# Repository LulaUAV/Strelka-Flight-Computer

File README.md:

# Strelka-Flight-Computer
Strelka exists in the family of rocket dog flight computers. This flight computer is fully capable of deploying recovery events.

Strelka (Стрелка, "little arrow") was a dog that spent a day in space aboard Korabl-Sputnik 2 (Sputnik 5) on 19 August 1960 before safely returning to Earth.

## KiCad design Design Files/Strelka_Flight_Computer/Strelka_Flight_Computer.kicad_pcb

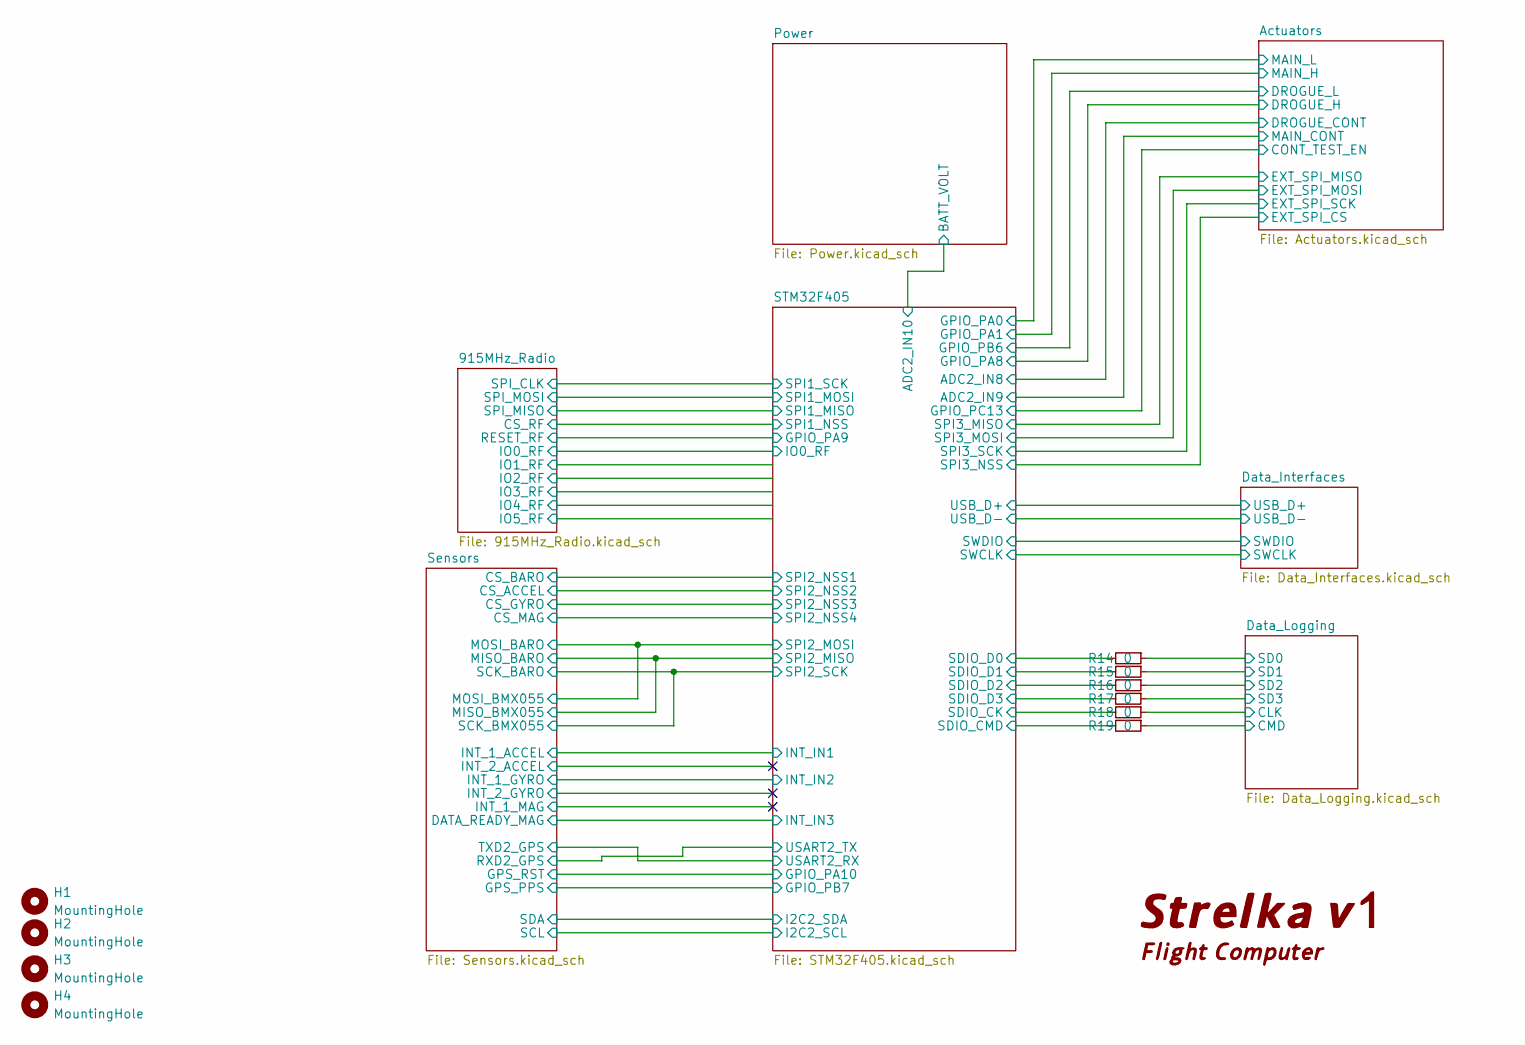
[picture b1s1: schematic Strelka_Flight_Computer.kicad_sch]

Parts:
H1, H2, H3, H4: MountingHole; MountingHole_2.5mm_Pad
R14, R15, R16, R17, R18, R19: 0; R_0603_1608Metric_Pad0.98x0.95mm_HandSolder

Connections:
/Data_Logging/CLK: R18.1; also elsewhere on the board
/Data_Logging/CMD: R19.1; also elsewhere on the board
/Data_Logging/SD0: R14.1; also elsewhere on the board
/Data_Logging/SD1: R15.1; also elsewhere on the board
/Data_Logging/SD2: R16.1; also elsewhere on the board
/Data_Logging/SD3: R17.1; also elsewhere on the board
/STM32F405/SDIO_CK: R18.2; also elsewhere on the board
/STM32F405/SDIO_CMD: R19.2; also elsewhere on the board
/STM32F405/SDIO_D0: R14.2; also elsewhere on the board
/STM32F405/SDIO_D1: R15.2; also elsewhere on the board
/STM32F405/SDIO_D2: R16.2; also elsewhere on the board
/STM32F405/SDIO_D3: R17.2; also elsewhere on the board

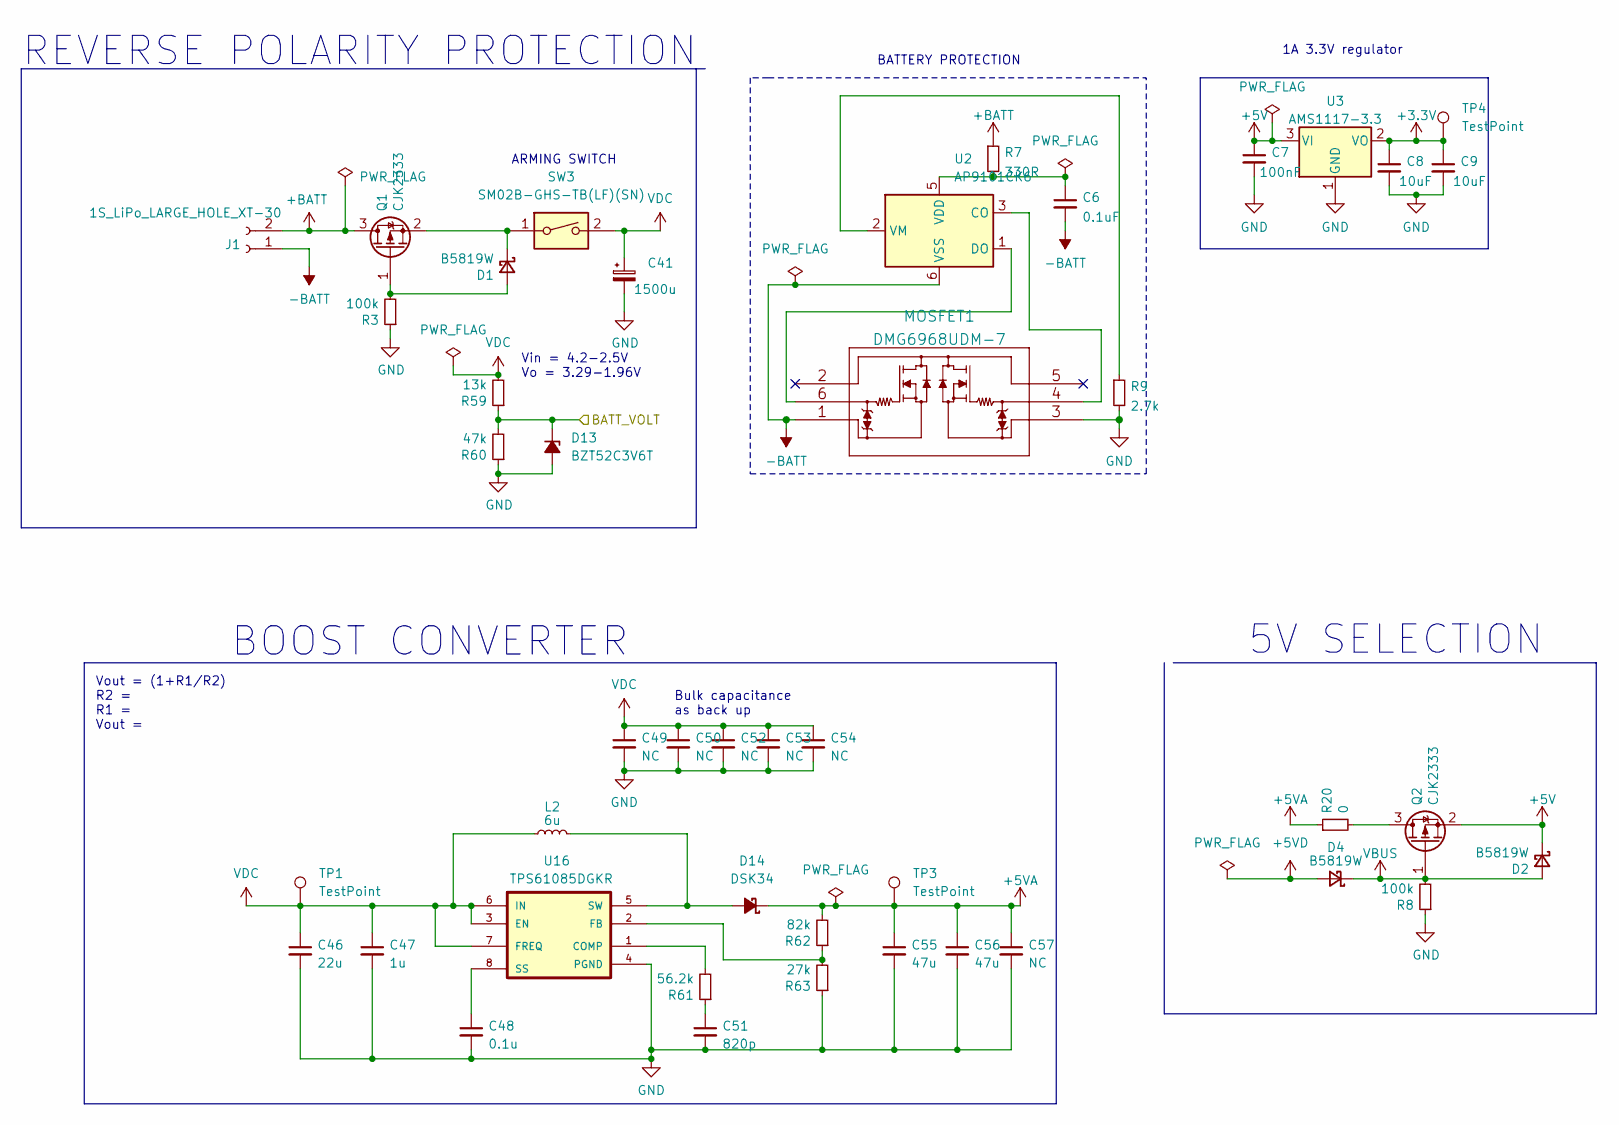
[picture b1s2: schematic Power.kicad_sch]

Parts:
C6: 0.1uF; C_0603_1608Metric
C7: 100nF; C_0603_1608Metric_Pad1.08x0.95mm_HandSolder
C8, C9: 10uF; C_0603_1608Metric_Pad1.08x0.95mm_HandSolder
C41: 1500u; ULR158M0JF1ARR; LCSC# C248440
C46: 22u; C_0603_1608Metric
C47: 1u; C_0603_1608Metric
C48: 0.1u; C_0603_1608Metric
C49, C50, C52, C53, C54: NC; C_0603_1608Metric
C51: 820p; C_0603_1608Metric
C55, C56: 47u; C_0805_2012Metric
C57: NC; C_0805_2012Metric
D1, D2, D4: B5819W; D_SOD-123; LCSC# C8598
D13: BZT52C3V6T; D_SOD-523; LCSC# C2858499
D14: DSK34; D_SOD-123; LCSC# C908230
J1: 1S_LiPo_LARGE_HOLE_XT-30; AMASS_XT30PW-M_1x02_P2.50mm_Horizontal
L2: 6u; L_Bourns_SRP5030T; LCSC# C1329837
MOSFET1: DMG6968UDM-7; LCSC# C151635
Q1, Q2: CJK2333; SOT-23; LCSC# C504109
R3, R8: 100k; R_0603_1608Metric
R7: 330R; R_0603_1608Metric
R9: 2.7k; R_0603_1608Metric
R20: 0; R_0603_1608Metric
R59: 13k; R_0603_1608Metric; LCSC# C137796
R60: 47k; R_0603_1608Metric; LCSC# C105579
R61: 56.2k; R_0603_1608Metric; LCSC# C105579
R62: 82k; R_0603_1608Metric; LCSC# C105579
R63: 27k; R_0603_1608Metric; LCSC# C105579
SW3: SM02B-GHS-TB(LF)(SN); SM02BGHSTBLFSN; LCSC# C189893
TP1, TP3, TP4: TestPoint; TestPoint_Pad_1.0x1.0mm
U2: AP9101CK6; SOT-23-6; LCSC# C151339
U3: AMS1117-3.3; SOT-223-3_TabPin2; LCSC# C173386
U16: TPS61085DGKR; SOP65P490X110-8N; LCSC# C113659

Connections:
+3V3: C8.1, C9.1, TP4.1, U3.2 (VO); also elsewhere on the board
+5V: C7.1, D2.1 (K), Q2.2 (S), U3.3 (VI)
+5VA: C55.1, C56.1, C57.1, D14.1 (K), R20.1, R62.2, TP3.1
+5VD: D4.2 (A); also elsewhere on the board
+BATT: J1.2, Q1.3 (D), R7.1
-BATT: C6.2, J1.1, MOSFET1.1 (S1), U2.6 (VSS)
/Power/BATT_VOLT: D13.1 (K), R59.1, R60.2; also elsewhere on the board
GND: C7.2, C8.2, C9.2, C41.2, C46.2, C47.2, C48.2, C49.2, C50.2, C51.2, C52.2, C53.2, C54.2, C55.2, C56.2, C57.2, D13.2 (A), MOSFET1.3 (S2), R3.1, R8.1, R9.2, R60.1, R63.1, U3.1 (GND), U16.4 (PGND); also elsewhere on the board
unnamed: C6.1, R7.2, U2.5 (VDD)
unnamed: C48.1, U16.8 (SS)
unnamed: C51.1, R61.1
unnamed: D1.1 (K), Q1.2 (S), SW3.1
unnamed: D1.2 (A), Q1.1 (G), R3.2
unnamed: D14.2 (A), L2.2, U16.5 (SW)
unnamed: MOSFET1.4 (G2), U2.3 (CO)
unnamed: MOSFET1.6 (G1), U2.1 (DO)
unnamed: Q2.3 (D), R20.2
unnamed: R9.1, U2.2 (VM)
unnamed: R61.2, U16.1 (COMP)
unnamed: R62.1, R63.2, U16.2 (FB)
VBUS: D2.2 (A), D4.1 (K), Q2.1 (G), R8.2; also elsewhere on the board
VDC: C41.1, C46.1, C47.1, C49.1, C50.1, C52.1, C53.1, C54.1, L2.1, R59.2, SW3.2, TP1.1, U16.3 (EN), U16.6 (IN), U16.7 (FREQ); also elsewhere on the board

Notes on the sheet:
5V SELECTION
BOOST CONVERTER
1A 3.3V regulator
REVERSE POLARITY PROTECTION
Vout = (1+R1/R2) R2 = R1 = Vout =
BATTERY PROTECTION
Bulk capacitance as back up
ARMING SWITCH
Vin = 4.2-2.5V Vo = 3.29-1.96V

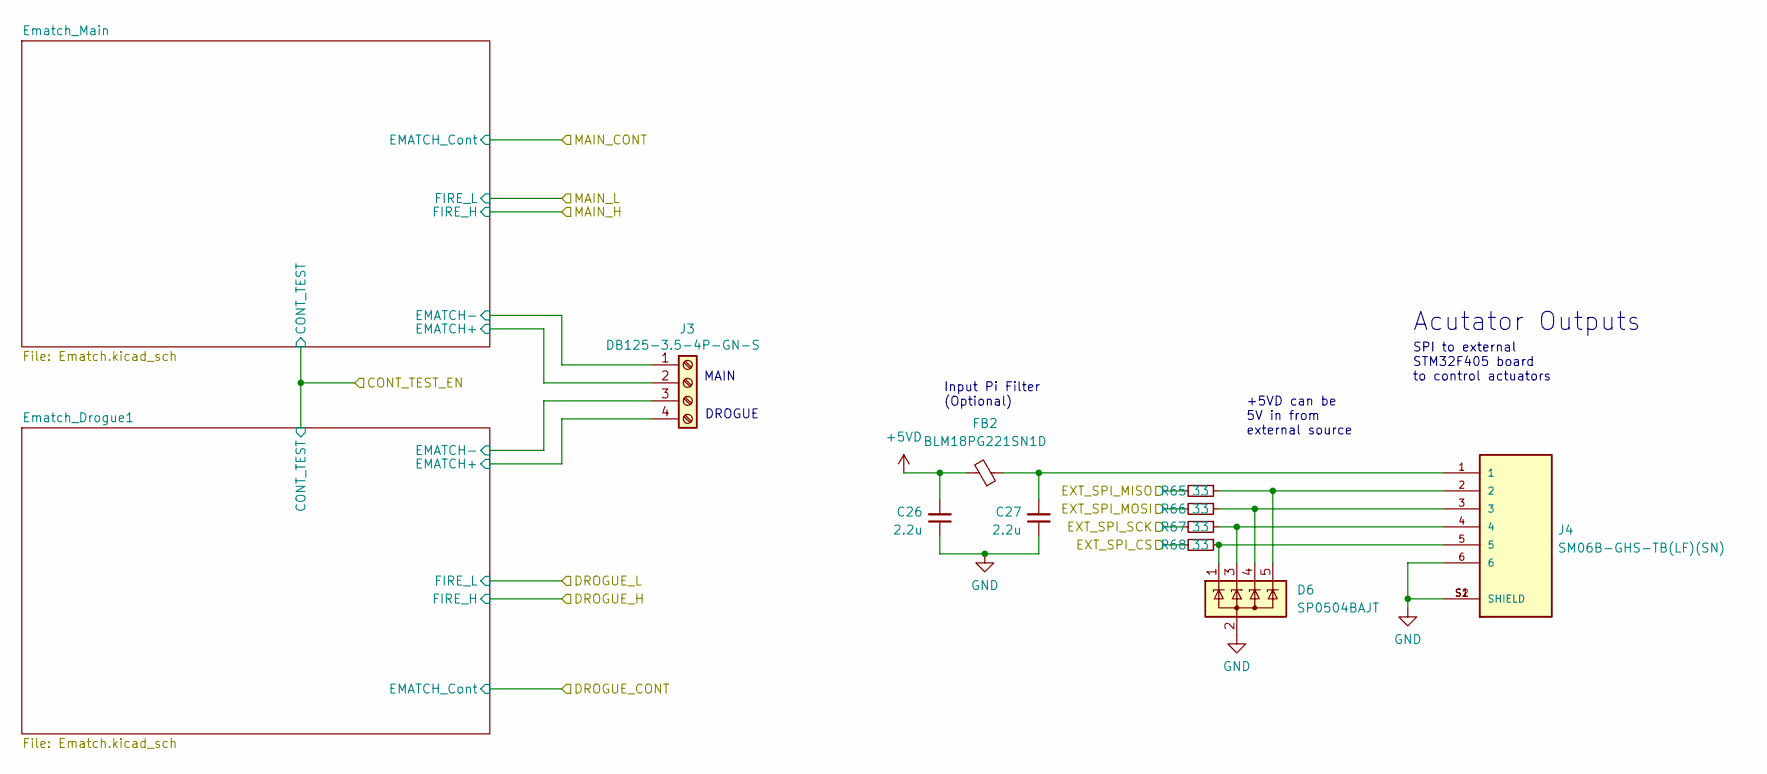
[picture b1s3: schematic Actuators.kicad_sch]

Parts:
C26, C27: 2.2u; C_0603_1608Metric
D6: SP0504BAJT; SOT-353_SC-70-5; LCSC# C5116451
FB2: BLM18PG221SN1D; L_0603_1608Metric; LCSC# C80165
J3: DB125-3.5-4P-GN-S; TerminalBlock_4Ucon_1x04_P3.50mm_Horizontal; LCSC# C2757925
J4: SM06B-GHS-TB(LF)(SN); JST_SM06B-GHS-TB(LF)(SN); LCSC# C133065
R65, R66, R67, R68: 33; R_0603_1608Metric_Pad0.98x0.95mm_HandSolder

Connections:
+5VD: C26.2, FB2.2; also elsewhere on the board
/Actuators/EXT_SPI_CS: R68.2; also elsewhere on the board
/Actuators/EXT_SPI_MISO: R65.2; also elsewhere on the board
/Actuators/EXT_SPI_MOSI: R66.2; also elsewhere on the board
/Actuators/EXT_SPI_SCK: R67.2; also elsewhere on the board
/Actuators/Ematch_Drogue1/EMATCH+: J3.4; also elsewhere on the board
/Actuators/Ematch_Drogue1/EMATCH-: J3.3; also elsewhere on the board
/Actuators/Ematch_Main/EMATCH+: J3.2; also elsewhere on the board
/Actuators/Ematch_Main/EMATCH-: J3.1; also elsewhere on the board
GND: C26.1, C27.1, D6.2 (A), J4.6, J4.S1 (SHIELD), J4.S2 (SHIELD); also elsewhere on the board
unnamed: C27.2, FB2.1, J4.1
unnamed: D6.1 (K), J4.5, R68.1
unnamed: D6.3 (K), J4.4, R67.1
unnamed: D6.4 (K), J4.3, R66.1
unnamed: D6.5 (K), J4.2, R65.1

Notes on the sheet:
DROGUE
+5VD can be 5V in from external source
Acutator Outputs
SPI to external STM32F405 board to control actuators
Input Pi Filter (Optional)
MAIN

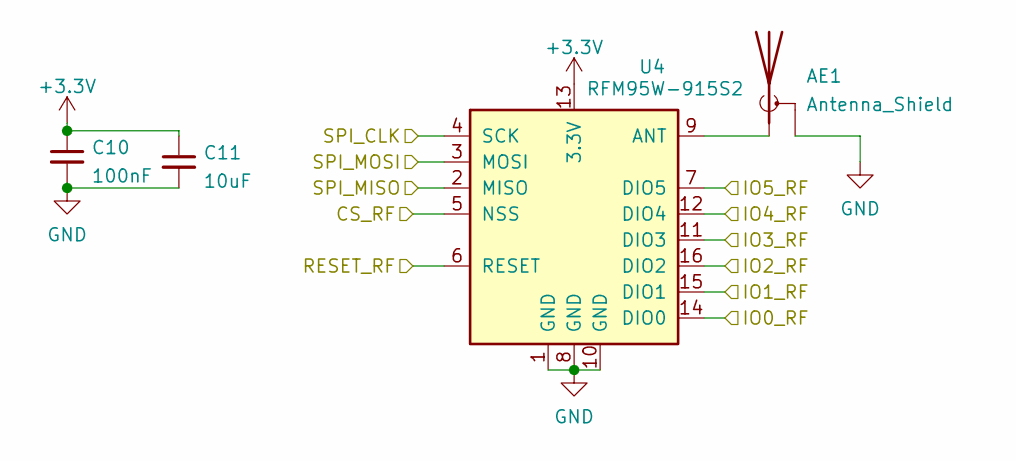
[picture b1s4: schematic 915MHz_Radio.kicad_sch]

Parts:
AE1: Antenna_Shield; SMA_Amphenol_132134_Vertical; LCSC# C496550
C10: 100nF; C_0603_1608Metric_Pad1.08x0.95mm_HandSolder
C11: 10uF; C_0603_1608Metric_Pad1.08x0.95mm_HandSolder
U4: RFM95W-915S2; HOPERF_RFM9XW_SMD; LCSC# C2844473

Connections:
+3V3: C10.1, C11.1, U4.13 (3.3V); also elsewhere on the board
/915MHz_Radio/CS_RF: U4.5 (NSS); also elsewhere on the board
/915MHz_Radio/IO0_RF: U4.14 (DIO0); also elsewhere on the board
/915MHz_Radio/IO1_RF: U4.15 (DIO1)
/915MHz_Radio/IO2_RF: U4.16 (DIO2)
/915MHz_Radio/IO3_RF: U4.11 (DIO3)
/915MHz_Radio/IO4_RF: U4.12 (DIO4)
/915MHz_Radio/IO5_RF: U4.7 (DIO5)
/915MHz_Radio/RESET_RF: U4.6 (RESET); also elsewhere on the board
/915MHz_Radio/SPI_CLK: U4.4 (SCK); also elsewhere on the board
/915MHz_Radio/SPI_MISO: U4.2 (MISO); also elsewhere on the board
/915MHz_Radio/SPI_MOSI: U4.3 (MOSI); also elsewhere on the board
GND: AE1.2 (Shield), C10.2, C11.2, U4.1 (GND), U4.8 (GND), U4.10 (GND); also elsewhere on the board
unnamed: AE1.1 (A), U4.9 (ANT)

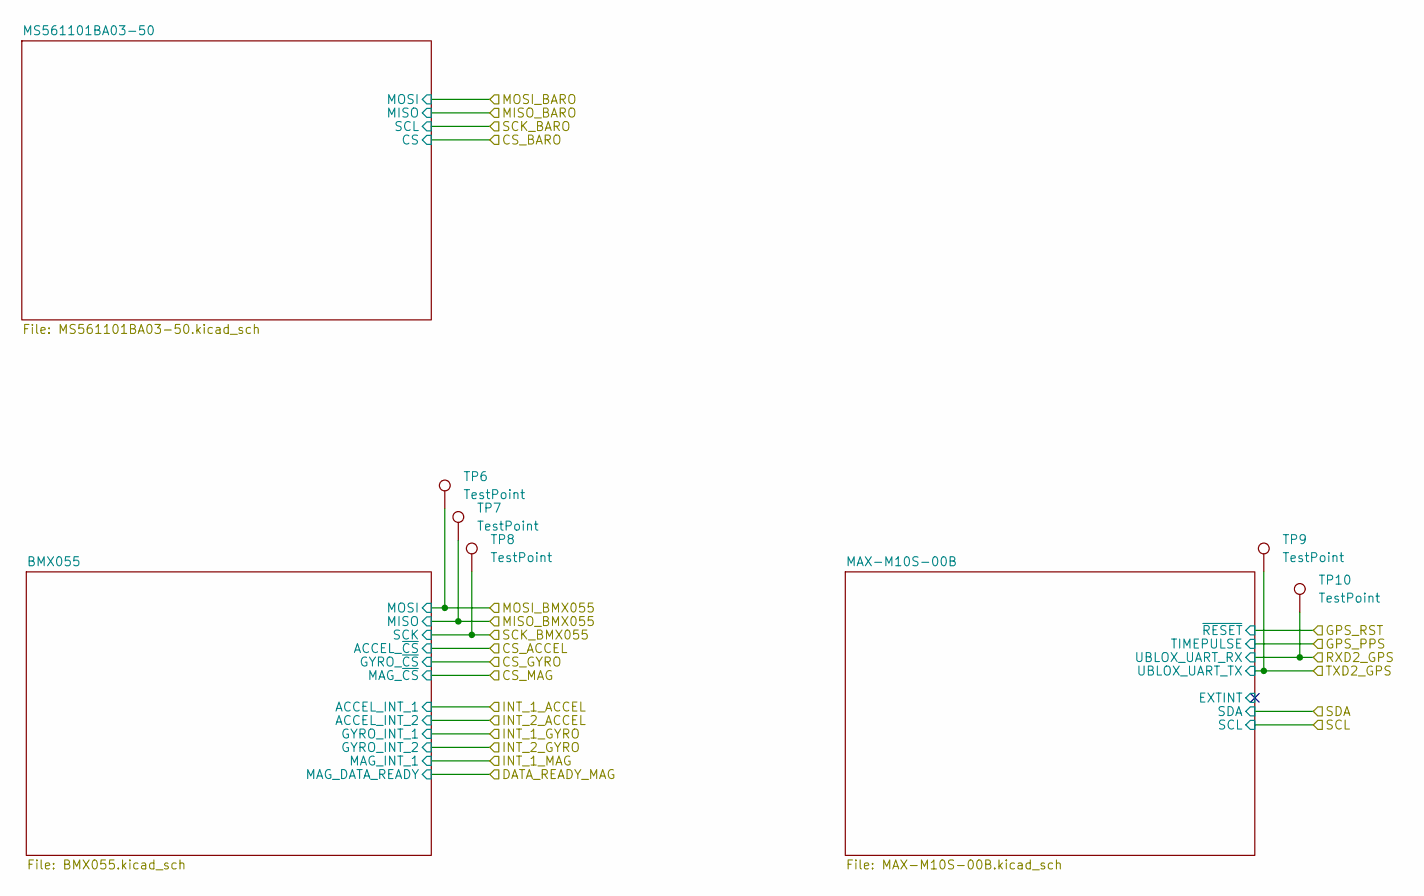
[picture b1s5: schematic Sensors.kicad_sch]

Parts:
TP6, TP7, TP8, TP9, TP10: TestPoint; TestPoint_Pad_1.0x1.0mm

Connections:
/STM32F405/SPI2_MISO: TP7.1; also elsewhere on the board
/STM32F405/SPI2_MOSI: TP6.1; also elsewhere on the board
/STM32F405/SPI2_SCK: TP8.1; also elsewhere on the board
/STM32F405/USART2_RX: TP9.1; also elsewhere on the board
/STM32F405/USART2_TX: TP10.1; also elsewhere on the board

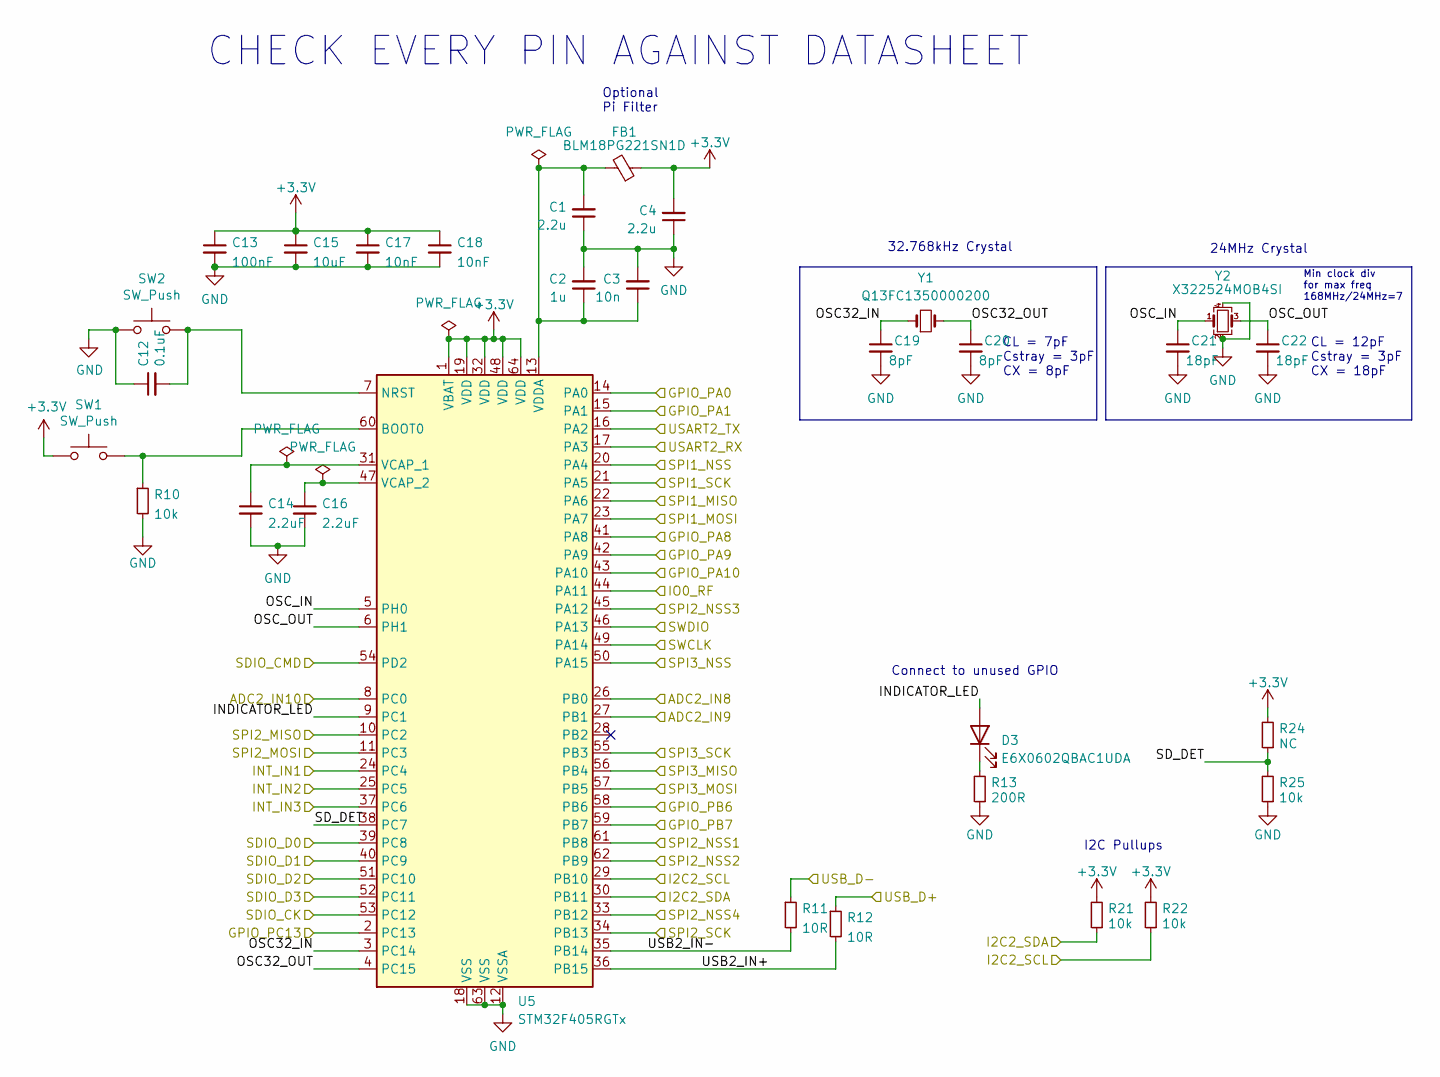
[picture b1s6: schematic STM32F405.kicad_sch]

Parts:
C1, C4: 2.2u; C_0603_1608Metric
C2: 1u; C_0603_1608Metric
C3: 10n; C_0603_1608Metric
C12: 0.1uF; C_0603_1608Metric_Pad1.08x0.95mm_HandSolder
C13: 100nF; C_0603_1608Metric_Pad1.08x0.95mm_HandSolder
C14, C16: 2.2uF; C_0603_1608Metric_Pad1.08x0.95mm_HandSolder
C15: 10uF; C_0603_1608Metric_Pad1.08x0.95mm_HandSolder
C17, C18: 10nF; C_0603_1608Metric_Pad1.08x0.95mm_HandSolder
C19, C20: 8pF; C_0603_1608Metric_Pad1.08x0.95mm_HandSolder
C21, C22: 18pF; C_0603_1608Metric_Pad1.08x0.95mm_HandSolder
D3: E6X0602QBAC1UDA; LED_0603_1608Metric_Pad1.05x0.95mm_HandSolder; LCSC# C375467
FB1: BLM18PG221SN1D; L_0603_1608Metric; LCSC# C80165
R10: 10k; R_0603_1608Metric
R11, R12: 10R; R_0603_1608Metric
R13: 200R; R_0603_1608Metric_Pad0.98x0.95mm_HandSolder
R21, R22, R25: 10k; R_0603_1608Metric_Pad0.98x0.95mm_HandSolder
R24: NC; R_0603_1608Metric_Pad0.98x0.95mm_HandSolder
SW1, SW2: SW_Push; SW_Push_SPST_NO_Alps_SKRK
U5: STM32F405RGTx; LQFP-64_10x10mm_P0.5mm; LCSC# C15742
Y1: Q13FC1350000200; Crystal_SMD_3215-2Pin_3.2x1.5mm; LCSC# C48615
Y2: X322524MOB4SI; Crystal_SMD_3225-4Pin_3.2x2.5mm; LCSC# C70590

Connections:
+3V3: C4.2, C13.1, C15.1, C17.1, C18.1, FB1.1, R21.2, R22.2, R24.2, SW1.1, U5.1 (VBAT), U5.19 (VDD), U5.32 (VDD), U5.48 (VDD), U5.64 (VDD); also elsewhere on the board
/915MHz_Radio/CS_RF: U5.20 (PA4); also elsewhere on the board
/915MHz_Radio/IO0_RF: U5.44 (PA11); also elsewhere on the board
/915MHz_Radio/RESET_RF: U5.42 (PA9); also elsewhere on the board
/915MHz_Radio/SPI_CLK: U5.21 (PA5); also elsewhere on the board
/915MHz_Radio/SPI_MISO: U5.22 (PA6); also elsewhere on the board
/915MHz_Radio/SPI_MOSI: U5.23 (PA7); also elsewhere on the board
/Actuators/CONT_TEST_EN: U5.2 (PC13); also elsewhere on the board
/Actuators/DROGUE_CONT: U5.26 (PB0); also elsewhere on the board
/Actuators/DROGUE_H: U5.41 (PA8); also elsewhere on the board
/Actuators/DROGUE_L: U5.58 (PB6); also elsewhere on the board
/Actuators/EXT_SPI_CS: U5.50 (PA15); also elsewhere on the board
/Actuators/EXT_SPI_MISO: U5.56 (PB4); also elsewhere on the board
/Actuators/EXT_SPI_MOSI: U5.57 (PB5); also elsewhere on the board
/Actuators/EXT_SPI_SCK: U5.55 (PB3); also elsewhere on the board
/Actuators/MAIN_CONT: U5.27 (PB1); also elsewhere on the board
/Actuators/MAIN_H: U5.15 (PA1); also elsewhere on the board
/Actuators/MAIN_L: U5.14 (PA0); also elsewhere on the board
/Data_Interfaces/SWCLK: U5.49 (PA14); also elsewhere on the board
/Data_Interfaces/SWDIO: U5.46 (PA13); also elsewhere on the board
/Data_Interfaces/USB_D+: R12.1; also elsewhere on the board
/Data_Interfaces/USB_D-: R11.1; also elsewhere on the board
/Power/BATT_VOLT: U5.8 (PC0); also elsewhere on the board
/STM32F405/GPIO_PA10: U5.43 (PA10); also elsewhere on the board
/STM32F405/GPIO_PB7: U5.59 (PB7); also elsewhere on the board
/STM32F405/I2C2_SCL: R22.1, U5.29 (PB10); also elsewhere on the board
/STM32F405/I2C2_SDA: R21.1, U5.30 (PB11); also elsewhere on the board
/STM32F405/INDICATOR_LED: D3.2 (A), U5.9 (PC1)
/STM32F405/INT_IN1: U5.24 (PC4); also elsewhere on the board
/STM32F405/INT_IN2: U5.25 (PC5); also elsewhere on the board
/STM32F405/INT_IN3: U5.37 (PC6); also elsewhere on the board
/STM32F405/OSC32_IN: C19.1, U5.3 (PC14), Y1.1
/STM32F405/OSC32_OUT: C20.1, U5.4 (PC15), Y1.2
/STM32F405/OSC_IN: C21.1, U5.5 (PH0), Y2.1
/STM32F405/OSC_OUT: C22.1, U5.6 (PH1), Y2.3
/STM32F405/SDIO_CK: U5.53 (PC12); also elsewhere on the board
/STM32F405/SDIO_CMD: U5.54 (PD2); also elsewhere on the board
/STM32F405/SDIO_D0: U5.39 (PC8); also elsewhere on the board
/STM32F405/SDIO_D1: U5.40 (PC9); also elsewhere on the board
/STM32F405/SDIO_D2: U5.51 (PC10); also elsewhere on the board
/STM32F405/SDIO_D3: U5.52 (PC11); also elsewhere on the board
/STM32F405/SD_DET: R24.1, R25.2, U5.38 (PC7)
/STM32F405/SPI2_MISO: U5.10 (PC2); also elsewhere on the board
/STM32F405/SPI2_MOSI: U5.11 (PC3); also elsewhere on the board
/STM32F405/SPI2_NSS1: U5.61 (PB8); also elsewhere on the board
/STM32F405/SPI2_NSS2: U5.62 (PB9); also elsewhere on the board
/STM32F405/SPI2_NSS3: U5.45 (PA12); also elsewhere on the board
/STM32F405/SPI2_NSS4: U5.33 (PB12); also elsewhere on the board
/STM32F405/SPI2_SCK: U5.34 (PB13); also elsewhere on the board
/STM32F405/USART2_RX: U5.17 (PA3); also elsewhere on the board
/STM32F405/USART2_TX: U5.16 (PA2); also elsewhere on the board
/STM32F405/USB2_IN+: R12.2, U5.36 (PB15)
/STM32F405/USB2_IN-: R11.2, U5.35 (PB14)
GND: C1.1, C2.2, C3.2, C4.1, C12.1, C13.2, C14.2, C15.2, C16.2, C17.2, C18.2, C19.2, C20.2, C21.2, C22.2, R10.2, R13.1, R25.1, SW2.1, U5.12 (VSSA), U5.18 (VSS), U5.63 (VSS), Y2.2, Y2.4; also elsewhere on the board
unnamed: C1.2, C2.1, C3.1, FB1.2, U5.13 (VDDA)
unnamed: C12.2, SW2.2, U5.7 (NRST)
unnamed: C14.1, U5.31 (VCAP_1)
unnamed: C16.1, U5.47 (VCAP_2)
unnamed: D3.1 (K), R13.2
unnamed: R10.1, SW1.2, U5.60 (BOOT0)

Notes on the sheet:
Connect to unused GPIO
24MHz Crystal
CL = 7pF Cstray = 3pF CX = 8pF
32.768kHz Crystal
I2C Pullups
CHECK EVERY PIN AGAINST DATASHEET
CL = 12pF Cstray = 3pF CX = 18pF
Optional Pi Filter
Min clock div for max freq 168MHz/24MHz=7

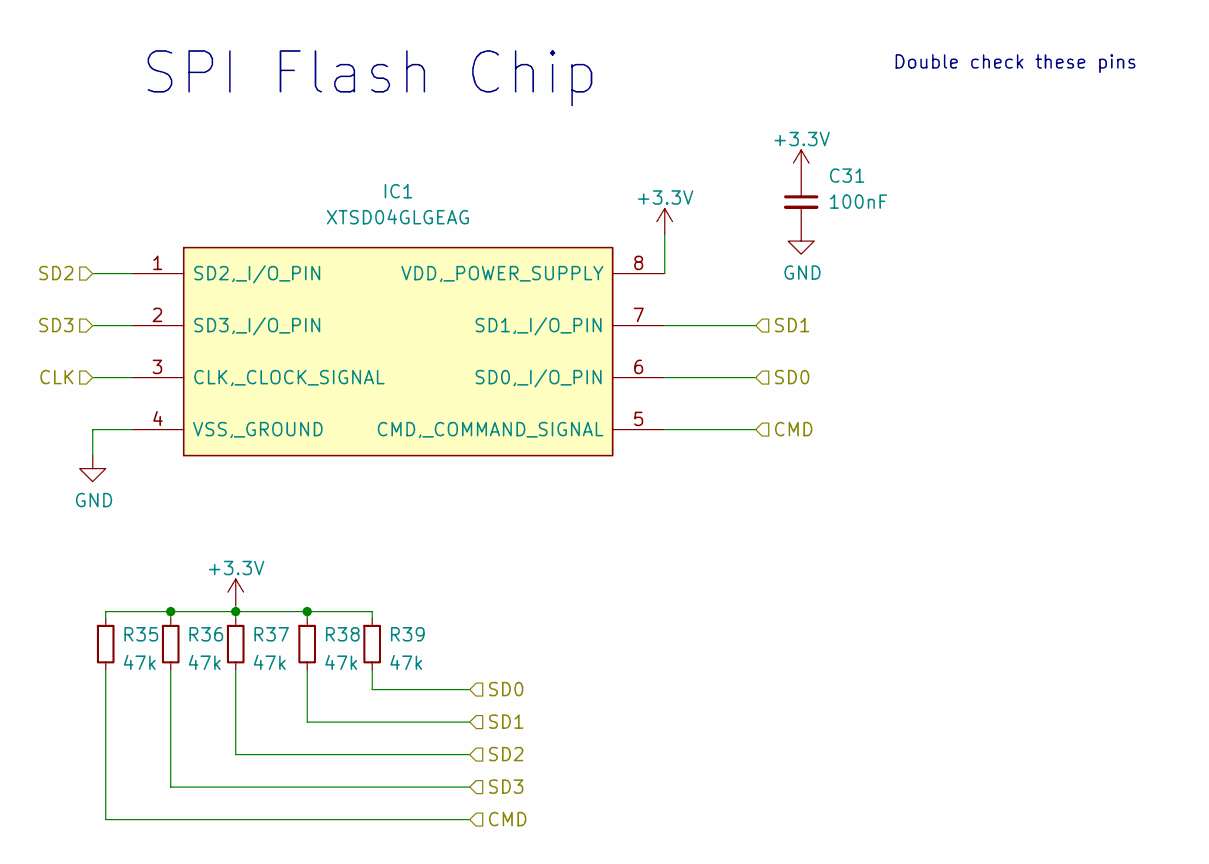
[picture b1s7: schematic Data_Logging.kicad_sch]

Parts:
C31: 100nF; C_0603_1608Metric
IC1: XTSD04GLGEAG; SON127P800X600X95-8N; LCSC# C558839
R35, R36, R37, R38, R39: 47k; R_0603_1608Metric

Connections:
+3V3: C31.1, IC1.8 (VDD,_POWER_SUPPLY), R35.1, R36.1, R37.1, R38.1, R39.1; also elsewhere on the board
/Data_Logging/CLK: IC1.3 (CLK,_CLOCK_SIGNAL); also elsewhere on the board
/Data_Logging/CMD: IC1.5 (CMD,_COMMAND_SIGNAL), R35.2; also elsewhere on the board
/Data_Logging/SD0: IC1.6 (SD0,_I/O_PIN), R39.2; also elsewhere on the board
/Data_Logging/SD1: IC1.7 (SD1,_I/O_PIN), R38.2; also elsewhere on the board
/Data_Logging/SD2: IC1.1 (SD2,_I/O_PIN), R37.2; also elsewhere on the board
/Data_Logging/SD3: IC1.2 (SD3,_I/O_PIN), R36.2; also elsewhere on the board
GND: C31.2, IC1.4 (VSS,_GROUND); also elsewhere on the board

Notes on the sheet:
SPI Flash Chip
Double check these pins

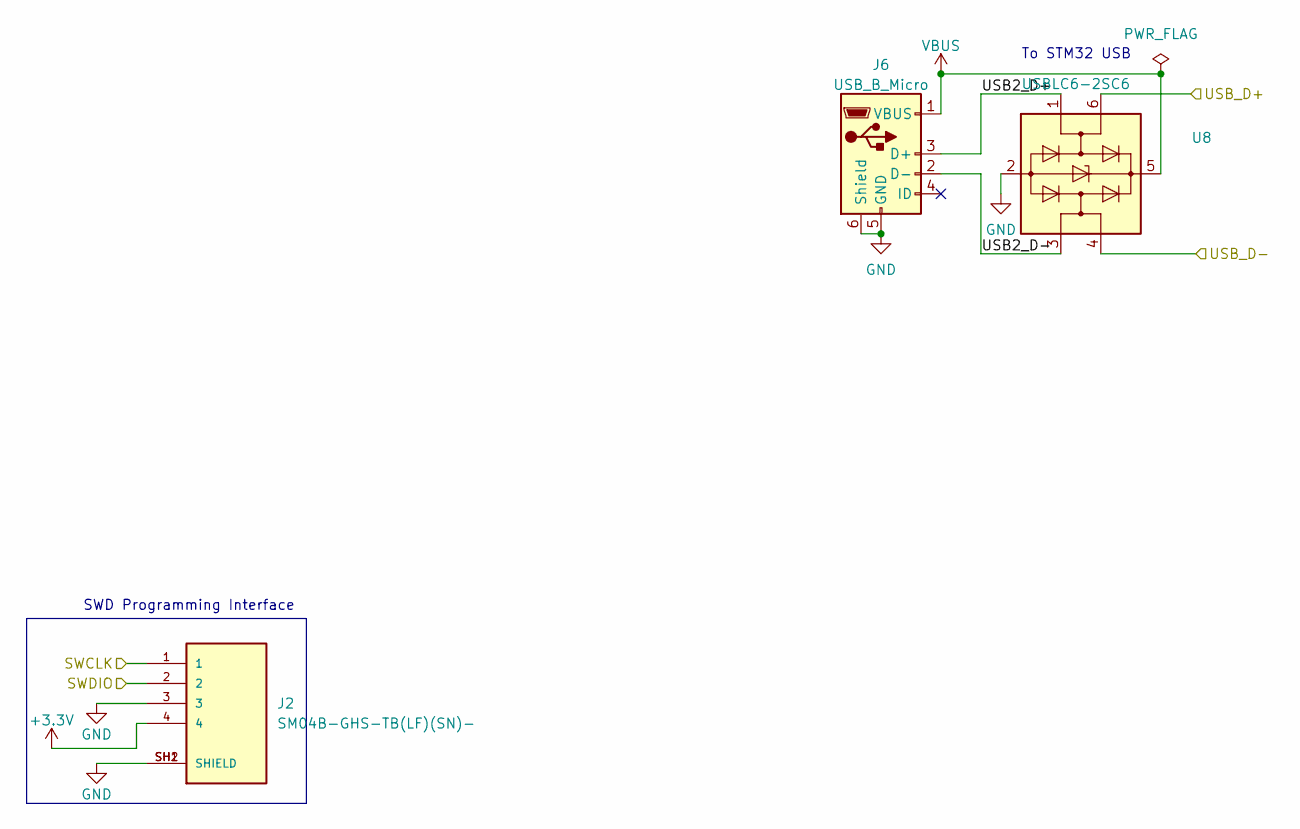
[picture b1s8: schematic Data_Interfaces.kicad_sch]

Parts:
J2: SM04B-GHS-TB(LF)(SN)-; JST_SM04B-GHS-TB(LF)(SN)-; LCSC# C189895
J6: USB_B_Micro; USB_Micro-B_Molex-105017-0001
U8: USBLC6-2SC6; SOT-23-6; LCSC# C2687116

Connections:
+3V3: J2.4; also elsewhere on the board
/Data_Interfaces/SWCLK: J2.1; also elsewhere on the board
/Data_Interfaces/SWDIO: J2.2; also elsewhere on the board
/Data_Interfaces/USB2_D+: J6.3 (D+), U8.1 (I/O1)
/Data_Interfaces/USB2_D-: J6.2 (D-), U8.3 (I/O2)
/Data_Interfaces/USB_D+: U8.6 (I/O1); also elsewhere on the board
/Data_Interfaces/USB_D-: U8.4 (I/O2); also elsewhere on the board
GND: J2.3, J2.SH1 (SHIELD), J2.SH2 (SHIELD), J6.5 (GND), J6.6 (Shield), U8.2 (GND); also elsewhere on the board
VBUS: J6.1 (VBUS), U8.5 (VBUS); also elsewhere on the board

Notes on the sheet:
To STM32 USB
SWD Programming Interface

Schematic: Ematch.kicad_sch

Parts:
D9: 1SS388; D_SOD-523; LCSC# C2987059
I2: AL5809-30S1-7; D_SOD-123; LCSC# C151325
Q8, Q9: AO3401A; SOT-23; LCSC# C347476
Q10: AP2300; SOT-23; LCSC# C360338
Q11: MMBT2222; SOT-23; LCSC# C8512
R47: 2R; R_2512_6332Metric; LCSC# C91926
R48, R51, R53, R54: 1k; R_0603_1608Metric
R49, R50, R52, R69: 100k; R_0603_1608Metric
U15: LM321; SOT-23-5; LCSC# C5189111

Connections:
+3V3: Q8.2 (S), R69.2, U15.2 (V-); also elsewhere on the board
/Actuators/CONT_TEST_EN: R48.2, R69.1; also elsewhere on the board
/Actuators/Ematch_Main/EMATCH+: D9.1 (K), Q9.3 (D), U15.1 (+); also elsewhere on the board
/Actuators/Ematch_Main/EMATCH-: Q10.3 (D); also elsewhere on the board
/Actuators/MAIN_CONT: R52.1, U15.4; also elsewhere on the board
/Actuators/MAIN_H: R53.2; also elsewhere on the board
/Actuators/MAIN_L: R50.2, R51.1; also elsewhere on the board
GND: Q10.2 (S), Q11.3 (E), R50.1, R54.1, U15.5 (V+); also elsewhere on the board
unnamed: D9.2 (A), I2.2
unnamed: I2.1, Q8.3 (D)
unnamed: Q8.1 (G), R48.1
unnamed: Q9.2 (S), R47.2
unnamed: Q10.1 (G), R51.2
unnamed: Q11.1 (B), R53.1
unnamed: Q9.1 (G), Q11.2 (C), R49.1
unnamed: R52.2, R54.2, U15.3 (-)
VDC: R47.1, R49.2; also elsewhere on the board

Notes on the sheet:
Continuity Test
Verify STM32 pins do not do weird shit at boot
Battery voltage applied
R_ematch: 1-2 Ohm R_limit = 2.0 Ohm Batt volt = 3V - 4.2V Fire current: Batt volt = 3.0V: R_ematch = 1 Ohm, I = 1.5A R_ematch = 2 Ohm, I = 0.75A Batt volt = 4.2V: R_ematch = 1 Ohm, I = 1.4AA R_ematch = 2 Ohm, I = 1.05A
To connector
Ematch Actuation

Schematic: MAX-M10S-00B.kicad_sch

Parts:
AE2: Antenna_Shield; U.FL_Hirose_U.FL-R-SMT-1_Vertical; LCSC# C88373
BT2: MS621FE-FL11E; BAT_MS621FE-FL11E
C36: 100n; C_0603_1608Metric
C37: NC; C_0402_1005Metric
C38: 4.7u; C_0603_1608Metric
C39: 100nF; C_0603_1608Metric
C40: 10uF; C_0603_1608Metric
D10: ESD9B3.3ST5G; D_0402_1005Metric; LCSC# C558621
D11: BAT54C; SOT-23; LCSC# C37704
D12: LED_BLUE; LED_0603_1608Metric
FB3: HZ1005K182TFB03; R_0402_1005Metric; LCSC# C279553
IC2: MAX-M10S-00B; MAXM10S00B
JP2: UART_Switch
R55: 0R; R_0402_1005Metric
R56, R57: 1k; R_0603_1608Metric
R58: 0R; R_0603_1608Metric

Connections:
+3V3: C39.1, C40.1, D11.1, IC2.7 (V_IO), IC2.8 (VCC); also elsewhere on the board
/STM32F405/GPIO_PA10: IC2.9 (RESET_N); also elsewhere on the board
/STM32F405/GPIO_PB7: R58.2; also elsewhere on the board
/STM32F405/I2C2_SCL: IC2.17 (SCL); also elsewhere on the board
/STM32F405/I2C2_SDA: IC2.16 (SDA); also elsewhere on the board
/STM32F405/USART2_RX: JP2.2 (TX1); also elsewhere on the board
/STM32F405/USART2_TX: JP2.4 (RX2); also elsewhere on the board
/Sensors/MAX-M10S-00B/EXTINT: IC2.5 (EXTINT)
/Sensors/MAX-M10S-00B/PPS: IC2.4 (TIMEPULSE), R57.1, R58.1
/Sensors/MAX-M10S-00B/RF_IN: AE2.1 (A), D10.2 (A2), FB3.1, IC2.11 (RF_IN)
/Sensors/MAX-M10S-00B/VCC_RF: C37.1, IC2.14 (VCC_RF), R55.1
/Sensors/MAX-M10S-00B/V_BKCP: BT2.+ (r~), C36.1, C38.1, IC2.6 (V_BCKP), R56.1
GND: AE2.2 (Shield), BT2.-, C36.2, C37.2, C38.2, C39.2, C40.2, D10.1 (A1), D12.1 (K), IC2.1 (GND_1), IC2.10 (GND_2), IC2.12 (GND_3); also elsewhere on the board
unnamed: D11.3, R56.2
unnamed: D12.2 (A), R57.2
unnamed: FB3.2, R55.2
unnamed: IC2.2 (TXD), JP2.3 (TX1)
unnamed: IC2.3 (RXD), JP2.1 (RX1)

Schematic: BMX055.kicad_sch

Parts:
C28, C29: 100nF; C_0603_1608Metric
R40: 0R; R_0603_1608Metric
U11: BMX055; LCSC# C94022

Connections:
+3V3: C28.1, C29.1, U11.3 (VDD), U11.13 (VDDIO); also elsewhere on the board
/STM32F405/INT_IN1: U11.19 (INT1); also elsewhere on the board
/STM32F405/INT_IN2: U11.14 (INT3); also elsewhere on the board
/STM32F405/INT_IN3: U11.2 (DRDYM); also elsewhere on the board
/STM32F405/SPI2_MISO: U11.12 (SDO2), U11.17 (SDO1); also elsewhere on the board
/STM32F405/SPI2_MOSI: U11.11 (SDX); also elsewhere on the board
/STM32F405/SPI2_NSS2: U11.16 (CSB1); also elsewhere on the board
/STM32F405/SPI2_NSS3: U11.5 (CSB2); also elsewhere on the board
/STM32F405/SPI2_NSS4: U11.20 (CSB3); also elsewhere on the board
/STM32F405/SPI2_SCK: U11.9 (SCX); also elsewhere on the board
/Sensors/INT_1_MAG: U11.10 (INT5)
/Sensors/INT_2_ACCEL: U11.1 (INT2)
/Sensors/INT_2_GYRO: U11.15 (INT4)
GND: C28.2, C29.2, R40.2, U11.4 (GNDA), U11.6 (GNDIO); also elsewhere on the board
unnamed: R40.1, U11.7 (PS)

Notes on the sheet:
Mag/Gyro/Accel
Tied low for SPI interface selection
Features: - Triaxial 16bit gyroscope - orientation- & motion inactivity recognition - Ranges switchable from ±125°/s to ±2000°/s - Low-pass filter bandwidths 230Hz - 12Hz - Integrated FIFO with a depth of 100 frames - Motion-triggered interrupt-signal generation - new data - any-motion (slope) dete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

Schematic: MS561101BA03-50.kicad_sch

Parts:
C30: 100nF; C_0603_1608Metric
U12: MS561101BA03-50

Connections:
+3V3: C30.1, U12.1 (VDD); also elsewhere on the board
/STM32F405/SPI2_MISO: U12.6 (SDO); also elsewhere on the board
/STM32F405/SPI2_MOSI: U12.7 (SDI/SDA); also elsewhere on the board
/STM32F405/SPI2_NSS1: U12.4 (CSB), U12.5 (CSB); also elsewhere on the board
/STM32F405/SPI2_SCK: U12.8 (SCLK); also elsewhere on the board
GND: C30.2, U12.2 (PS), U12.3 (GND); also elsewhere on the board

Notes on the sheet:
Barometer
Features: - Range 10-1200mbar +20,000m - -1449.98m - Resolution 24bit - Accuracy +-1.5mbar - Resolution 0.065 / 0.042 / 0.027 / 0.018 / 0.012mbar - Error band +-3.5mbar - Altitude res 0.1m

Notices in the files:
parts and their libraries:
Copyright 2016 Accelerated Designs. All rights reserved.
